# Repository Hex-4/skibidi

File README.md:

# The Skibidi Soundboard

<details>
<summary>Gen Alpha Translation (generated with ChatGPT)</summary>
  <br>
Ngl ts pmo fr 🫠  
This device? <b>STRAIGHT FROM OHIO</b> 🚽💀  

Built w/ that RP2040 RIZZ CHIP 🧠💪  

u press a button = **skibidi skibidi yes yes**  
u press TWO?? 💥  
bro summoned da *GigaChad Toilets vs CameraMan war pt. 9000* 💃📷💣  

It got:  
- ✨RGB RIZZ LIGHTS✨  
- 📢 NPC ear-shatter SFX  
- 😭 Your friends leaving u on Delivered  
- 🤓 Built-in Anti-Ohio containment breach (not working)

Made this on no sleep, 4 energy drinks, & a dream 💭  
Sigma device for Alpha minds. fr.  
if u ain’t pressing this on the bus at 6am do u even **GRIND**?

honestly? this thing go *stupid dumb goofy ahh*  
click one button and it’s OVER for society 🧍‍♂️

🫠🫠🫠  
full mental breakdown log in the [journal](JOURNAL.md) if u tryna go brain dead w/ me  

**Skibidi out.** 🧻💀🌸

</details>

<hr>

This is an RP2040-powered portable soundboard with buttons, RGB, and a speaker to play annoying sounds for my friends.

See how I built it in the [journal](JOURNAL.md).

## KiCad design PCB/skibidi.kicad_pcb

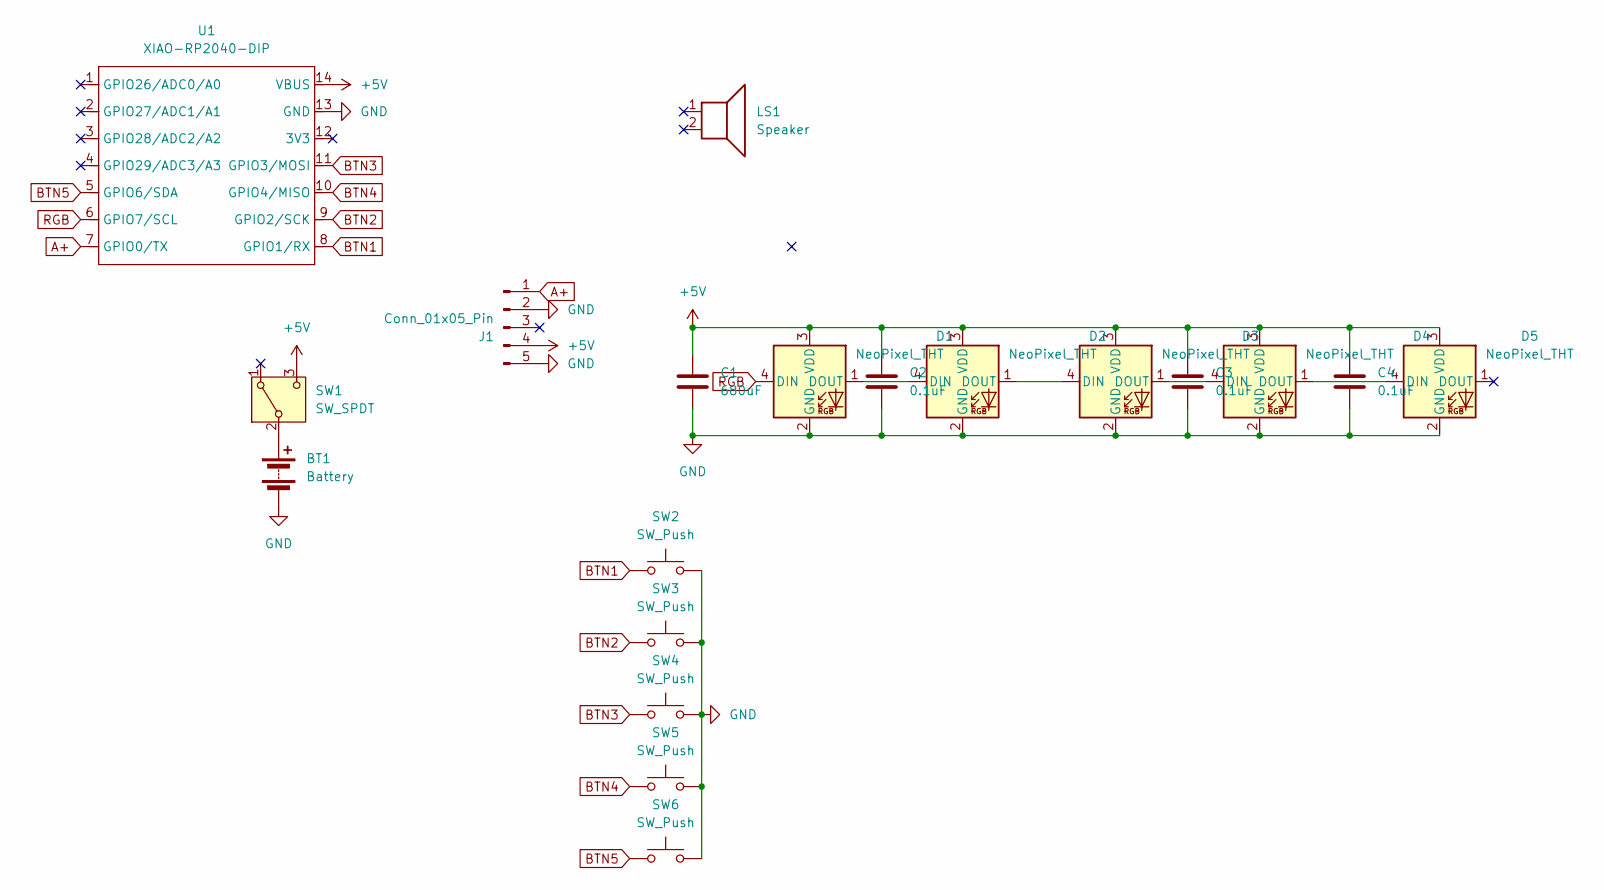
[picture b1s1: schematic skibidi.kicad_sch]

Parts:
BT1: Battery; JST_PH_S2B-PH-K_1x02_P2.00mm_Horizontal
C1: 680uF; CP_Radial_D8.0mm_P3.50mm
C2, C3, C4: 0.1uF; CP_Radial_D5.0mm_P2.50mm
D1, D2, D3, D4, D5: NeoPixel_THT; LED_D5.0mm-4_RGB_Staggered_Pins
J1: Conn_01x05_Pin; PinSocket_1x05_P2.54mm_Horizontal
LS1: Speaker
SW1: SW_SPDT; SW_E-Switch_EG1271_SPDT
SW2, SW3, SW4, SW5, SW6: SW_Push; SW_PUSH-12mm_Wuerth-430476085716
U1: XIAO-RP2040-DIP

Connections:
+5V: C1.1, C2.1, C3.1, C4.1, D1.3 (VDD), D2.3 (VDD), D3.3 (VDD), D4.3 (VDD), D5.3 (VDD), J1.4, SW1.3 (C), U1.14 (VBUS)
A+: J1.1, U1.7 (GPIO0/TX)
BTN1: SW2.1, U1.8 (GPIO1/RX)
BTN2: SW3.1, U1.9 (GPIO2/SCK)
BTN3: SW4.1, U1.11 (GPIO3/MOSI)
BTN4: SW5.1, U1.10 (GPIO4/MISO)
BTN5: SW6.1, U1.5 (GPIO6/SDA)
GND: BT1.2 (-), C1.2, C2.2, C3.2, C4.2, D1.2 (GND), D2.2 (GND), D3.2 (GND), D4.2 (GND), D5.2 (GND), J1.2, J1.5, SW2.2, SW3.2, SW4.2, SW5.2, SW6.2, U1.13 (GND)
unnamed: BT1.1 (+), SW1.2 (B)
unnamed: D1.1 (DOUT), D2.4 (DIN)
unnamed: D2.1 (DOUT), D3.4 (DIN)
unnamed: D3.1 (DOUT), D4.4 (DIN)
unnamed: D4.1 (DOUT), D5.4 (DIN)
RGB: D1.4 (DIN), U1.6 (GPIO7/SCL)

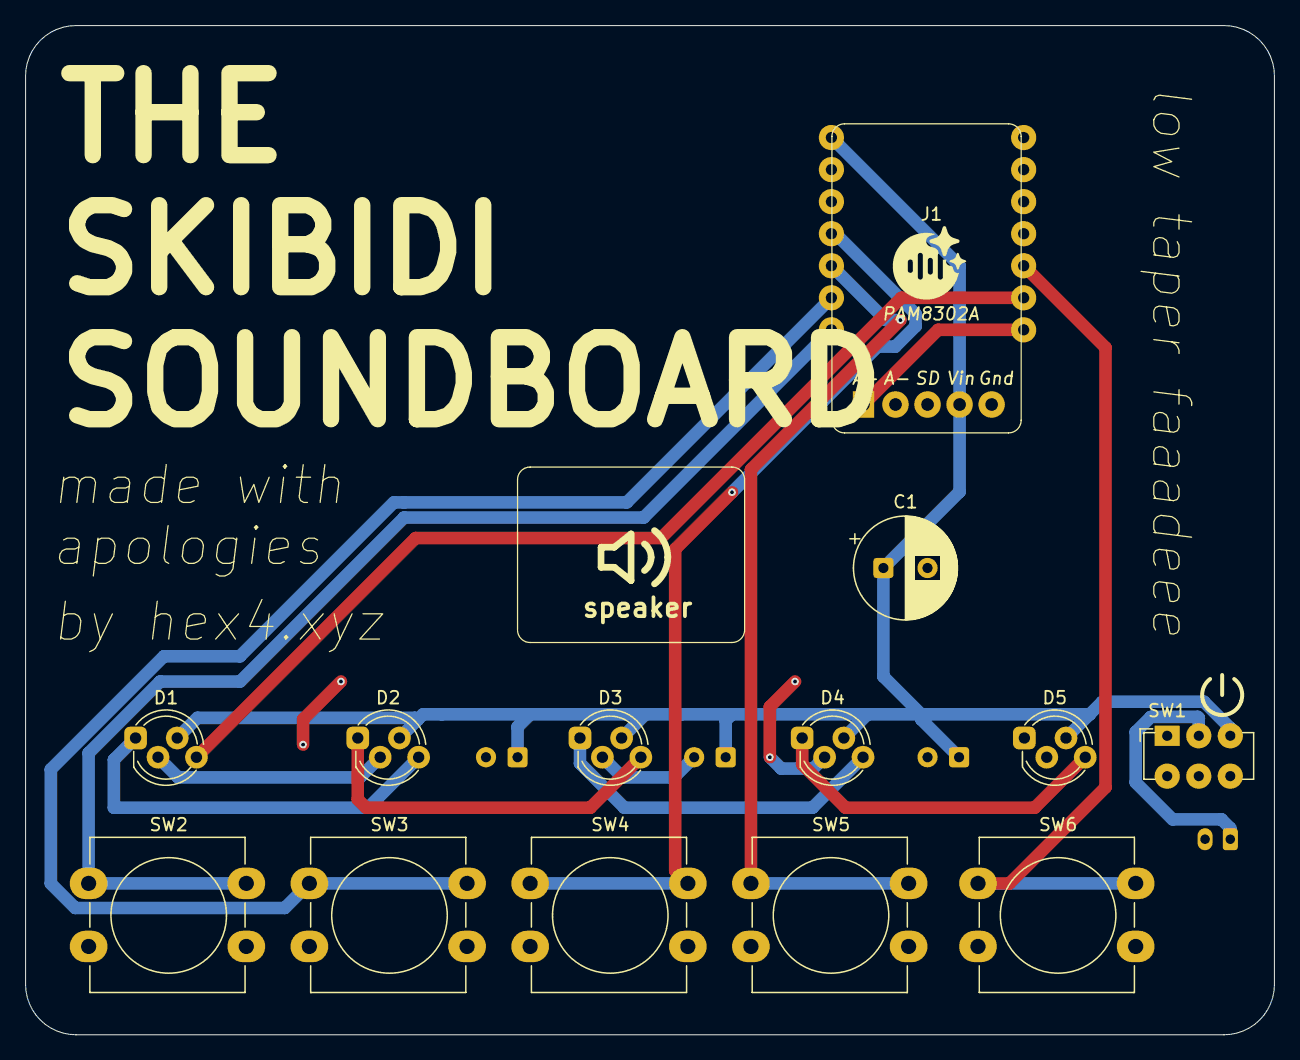
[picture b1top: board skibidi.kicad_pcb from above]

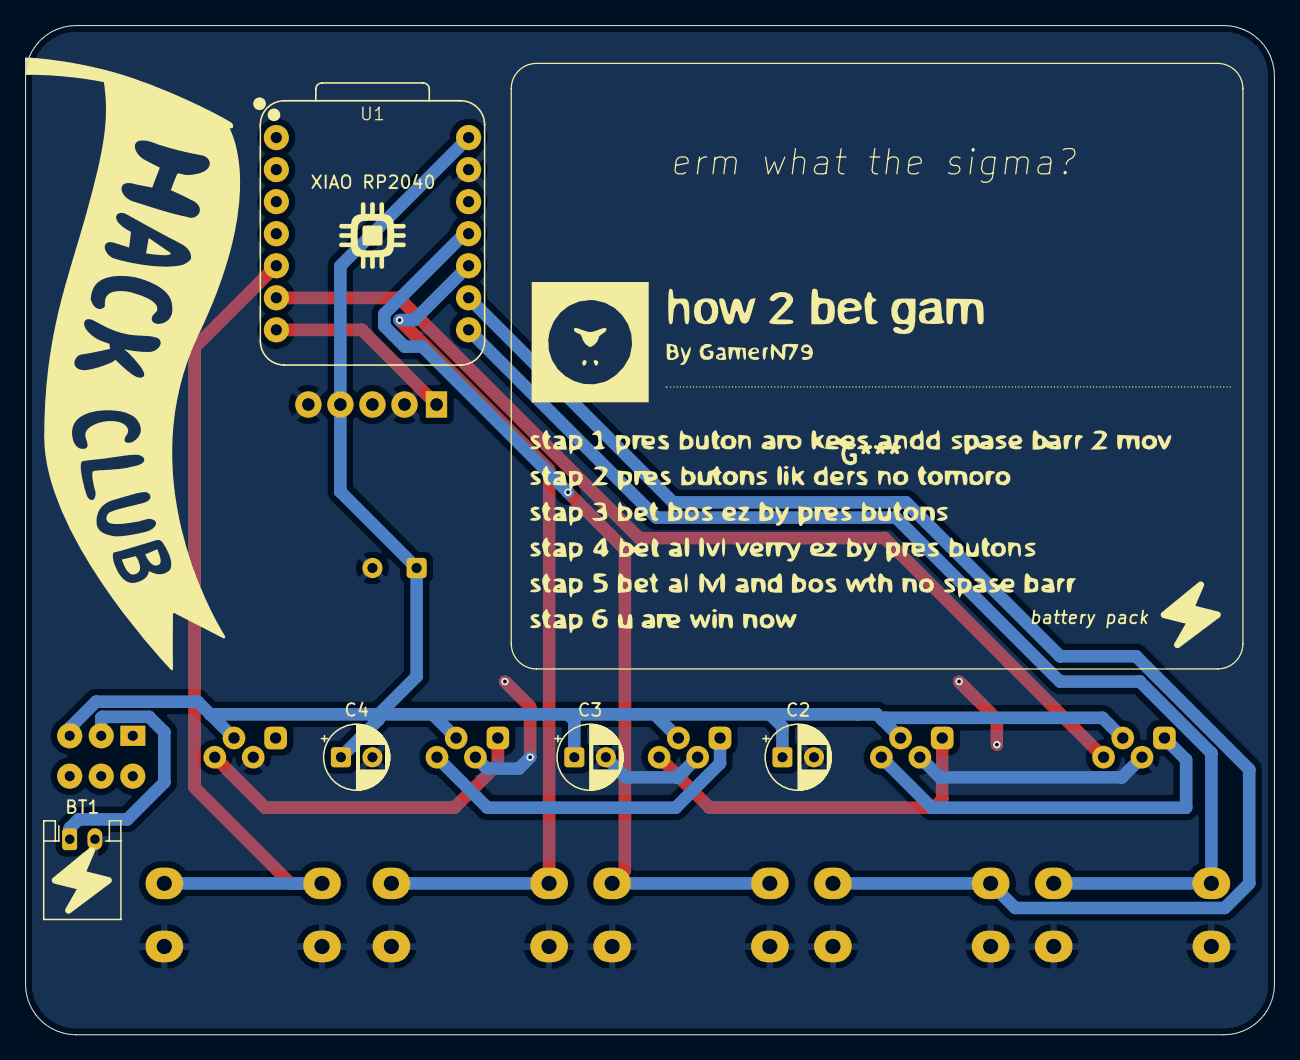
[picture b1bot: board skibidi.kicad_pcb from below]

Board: 2 copper layers, 99.0 x 80.0 mm, 18 parts (5 on the bottom side), 14 nets.

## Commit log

2025-07-04 Add a beta README, will mew to upgrade it later
2025-07-04 Session 1
2025-07-05 Session 2: Journal
2025-07-05 Session 2
2025-07-05 Session 3: Journal
2025-07-05 Session 3
2025-07-06 Session 4: Journal
2025-07-06 Session 4
